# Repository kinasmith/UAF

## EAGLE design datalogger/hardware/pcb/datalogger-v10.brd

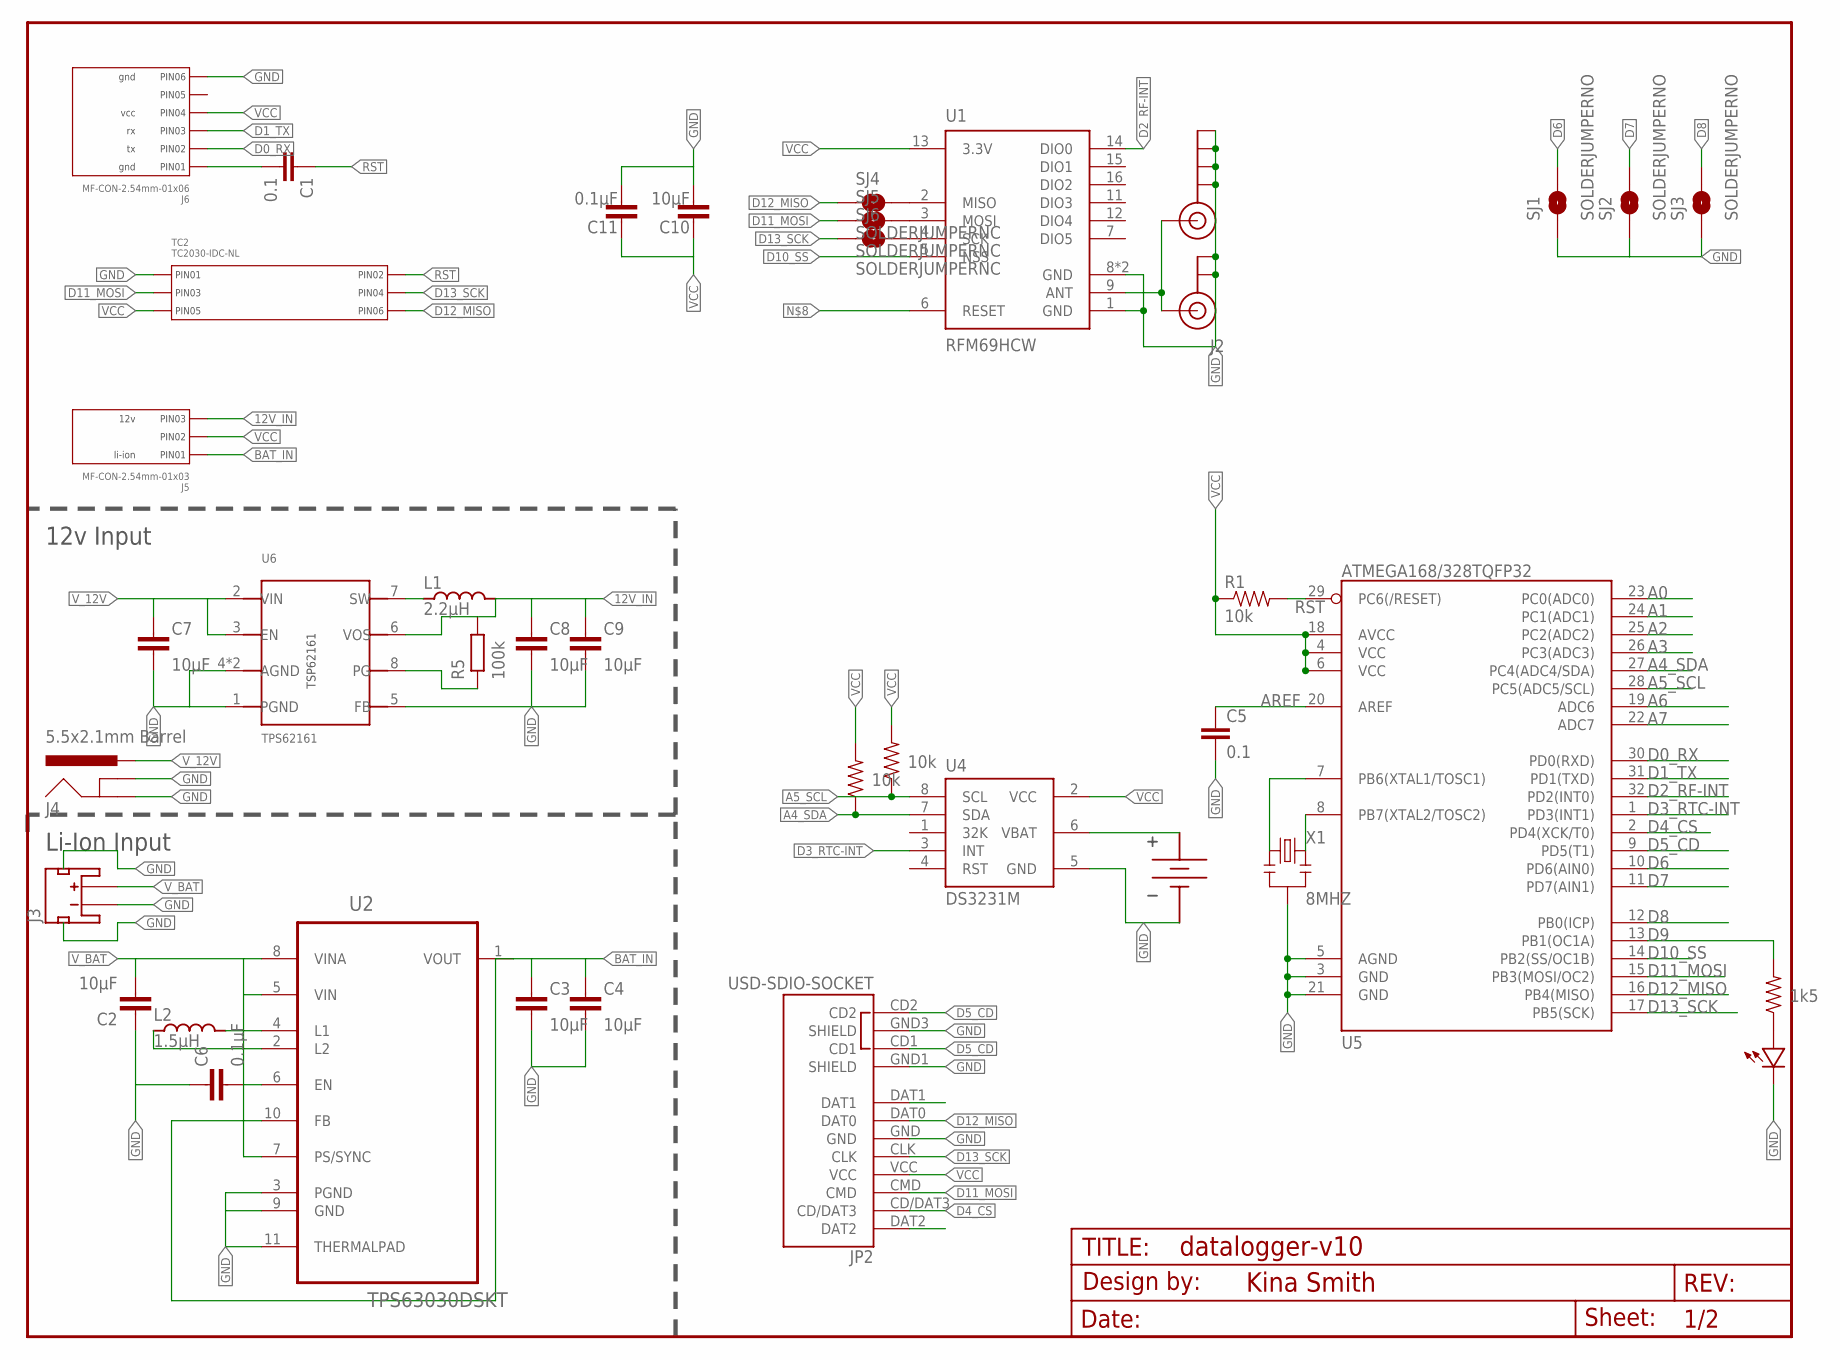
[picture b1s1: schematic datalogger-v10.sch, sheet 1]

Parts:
C1, C5: 0.1; 0603-CAP
C2, C3, C4, C7, C8, C9, C10: 10µF; C0805-N
C6, C11: 0.1µF; C0603-N
FRAME1: FRAME-LETTERNO_PACKAGE; DUMMY
J2: U.FL
J3: JST_2MM_MALE; JST-2-SMD
J4: 5.5x2.1mm Barrel; POWER_JACK_SMD
J5: MF-CON-2.54mm-01x03; PTH_2.54MM_01X03
J6: MF-CON-2.54mm-01x06; PTH_2.54MM_01X06
J$1: SMA_EDGE; SMA-EDGE
JP2: USD-SDIO-SOCKET; MICRO-SD-SOCKET-SDIO
L1: 2.2µH; IND_2.5X2
L2: 1.5µH; IND_3X3
R1, R3, R4: 10k; 0603-RES
R2: 1k5; 0603-RES
R5: 100k; R0603-N
SJ1, SJ2, SJ3: SOLDERJUMPERNO; SJ_2S-NO
SJ4, SJ5, SJ6: SOLDERJUMPERNC; SJ_2S
TC2: TC2030-IDC-NL
U1: RFM69HCW; RFM69HCW-XXXS2
U2: TPS63030DSKT; SON50P260X260X80-11N
U4: DS3231M; SO08
U5: ATMEGA168/328TQFP32; TQFP32-08
U6: TPS62161; WSON-8
U$1: BATTERY_HOLDER12MM; BATTCON_12MM
U$2: LED0603; 0603-LED
X1: 8MHZ; RESONATOR-SMD

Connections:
3V3L1: L2.P$2, U2.4 (L1)
3V3L2: L2.P$1, U2.2 (L2)
12V_IN: C8.1, C9.1, J5.P$3 (PIN3), L1.P$2, R5.2, U6.6 (VOS)
A0: U5.23 (PC0(ADC0))
A1: U5.24 (PC1(ADC1))
A2: U5.25 (PC2(ADC2))
A3: U5.26 (PC3(ADC3))
A4_SDA: R4.1, U4.7 (SDA), U5.27 (PC4(ADC4/SDA))
A5_SCL: R3.1, U4.8 (SCL), U5.28 (PC5(ADC5/SCL))
A6: U5.19 (ADC6)
A7: U5.22 (ADC7)
ANT: J2.P$3 (SIGNAL), J$1.SIG (SIGNAL), U1.9 (ANT)
AREF: C5.1, U5.20 (AREF)
BAT_IN: C3.1, C4.1, J5.P$1 (PIN1), U2.1 (VOUT), U2.10 (FB)
D0_RX: J6.P$2 (PIN2), U5.30 (PD0(RXD))
D1_TX: J6.P$3 (PIN3), U5.31 (PD1(TXD))
D2_RF-INT: U1.14 (DIO0), U5.32 (PD2(INT0))
D3_RTC-INT: U4.3 (INT), U5.1 (PD3(INT1))
D4_CS: JP2.CD/DAT3, U5.2 (PD4(XCK/T0))
D5_CD: JP2.CD1, JP2.CD2, U5.9 (PD5(T1))
D6: SJ1.2, U5.10 (PD6(AIN0))
D7: SJ2.2, U5.11 (PD7(AIN1))
D8: SJ3.2, U5.12 (PB0(ICP))
D9: R2.2, U5.13 (PB1(OC1A))
D10_SS: U1.5 (NSS), U5.14 (PB2(SS/OC1B))
D11_MOSI: JP2.CMD, SJ5.1, TC2.P$3 (PIN3), U5.15 (PB3(MOSI/OC2))
D12_MISO: JP2.DAT0, SJ4.1, TC2.P$6 (PIN6), U5.16 (PB4(MISO))
D13_SCK: JP2.CLK, SJ6.1, TC2.P$4 (PIN4), U5.17 (PB5(SCK))
GND: C2.1, C3.2, C4.2, C5.2, C6.1, C7.2, C8.2, C9.2, C10.2, C11.2, J2.P$1 (GND), J2.P$2 (GND), J3.1 (-), J3.NC1 (PAD1), J3.NC2 (PAD2), J4.GND (GNDBREAK), J4.P$4 (GND), J6.P$6 (PIN6), J$1.GND@0 (GND), J$1.GND@1 (GND), J$1.GND@2 (GND), J$1.GND@3 (GND), JP2.GND, JP2.GND1 (SHIELD), JP2.GND3 (SHIELD), SJ1.1, SJ2.1, SJ3.1, TC2.P$1 (PIN1), U1.1 (GND), U1.8 (GND), U1.10 (GND), U2.3 (PGND), U2.9 (GND), U2.11 (THERMALPAD), U4.5 (GND), U5.3 (GND), U5.5 (AGND), U5.21 (GND), U6.1 (PGND), U6.4 (AGND), U6.5 (FB), U6.P$9 (AGND), U$1.GND, U$2.MINUS, X1.2
unnamed: U5.7 (PB6(XTAL1/TOSC1)), X1.1
unnamed: R2.1, U$2.PLUS
unnamed: C1.2, J6.P$1 (PIN1)
unnamed: SJ4.2, U1.2 (MISO)
unnamed: SJ5.2, U1.3 (MOSI)
unnamed: U4.6 (VBAT), U$1.PWR@1 (VBAT), U$1.PWR@2 (VBAT)
unnamed: SJ6.2, U1.4 (SCK)
unnamed: R5.1, U6.8 (PG)
unnamed: U5.8 (PB7(XTAL2/TOSC2)), X1.3
RST: C1.1, R1.2, TC2.P$2 (PIN2), U5.29 (PC6(/RESET))
SW: L1.P$1, U6.7 (SW)
VCC: C10.1, C11.1, J5.P$2 (PIN2), J6.P$4 (PIN4), JP2.VCC, R1.1, R3.2, R4.2, TC2.P$5 (PIN5), U1.13 (3.3V), U4.2 (VCC), U5.4 (VCC), U5.6 (VCC), U5.18 (AVCC)
V_12V: C7.1, J4.VIN0 (PWR), U6.2 (VIN), U6.3 (EN)
V_BAT: C2.2, C6.2, J3.2 (+), U2.5 (VIN), U2.6 (EN), U2.7 (PS/SYNC), U2.8 (VINA)

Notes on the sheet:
12v Input
Li-Ion Input

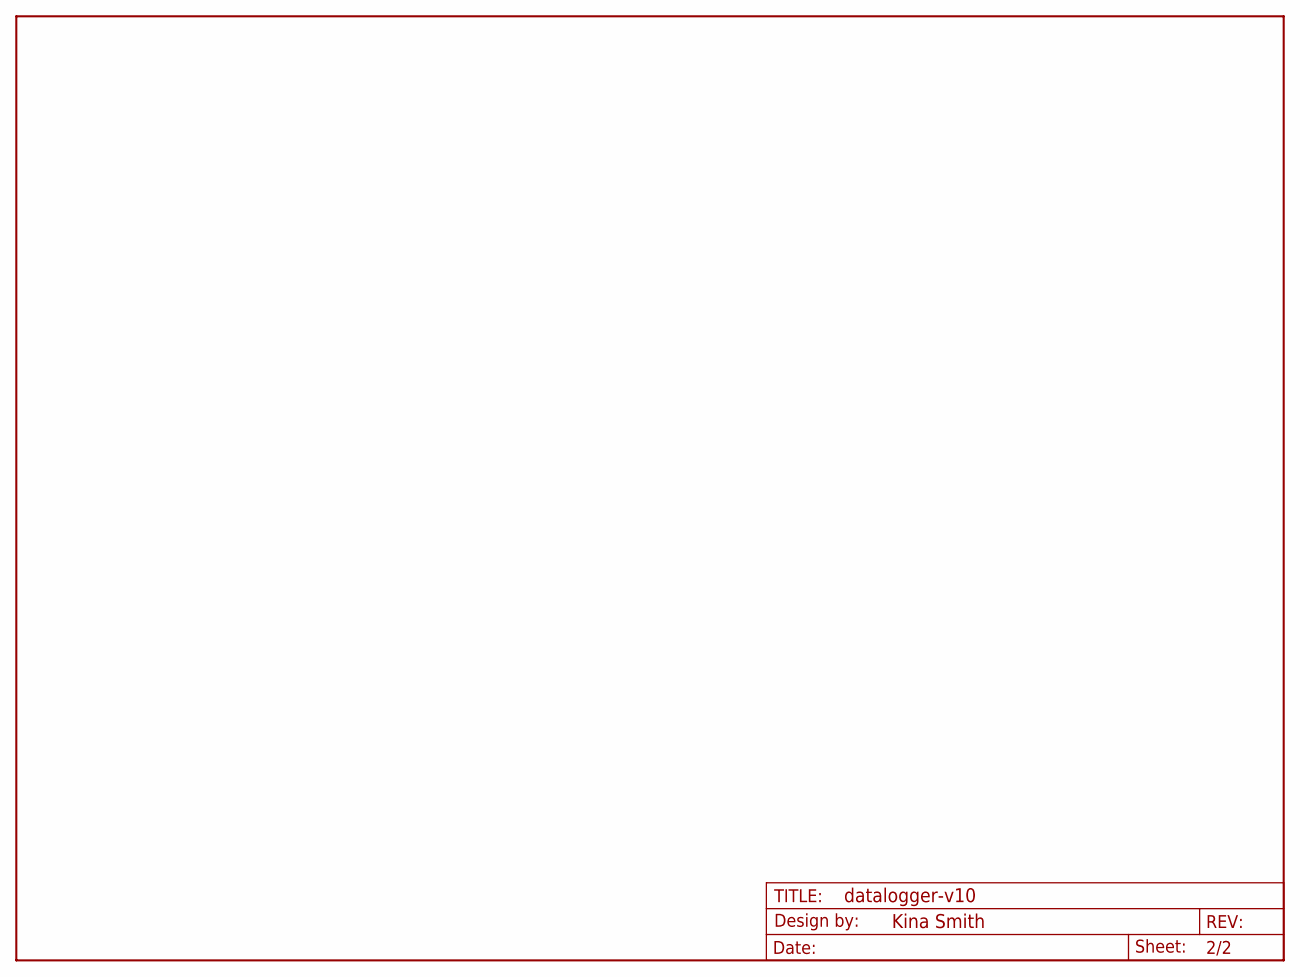
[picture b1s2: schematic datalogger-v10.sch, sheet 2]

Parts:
FRAME3: FRAME-LETTERNO_PACKAGE; DUMMY

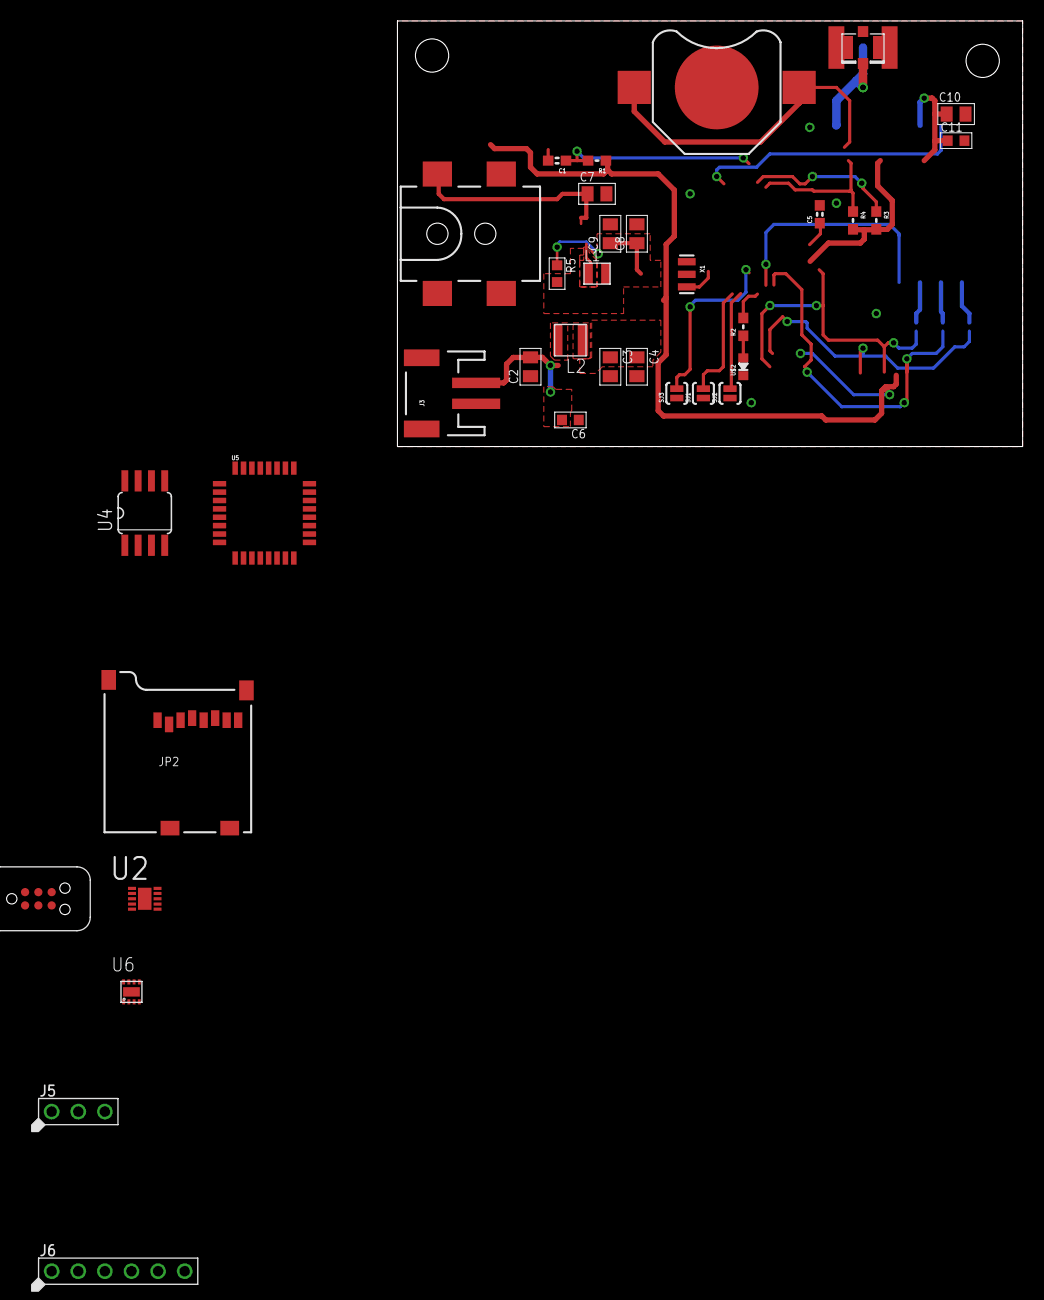
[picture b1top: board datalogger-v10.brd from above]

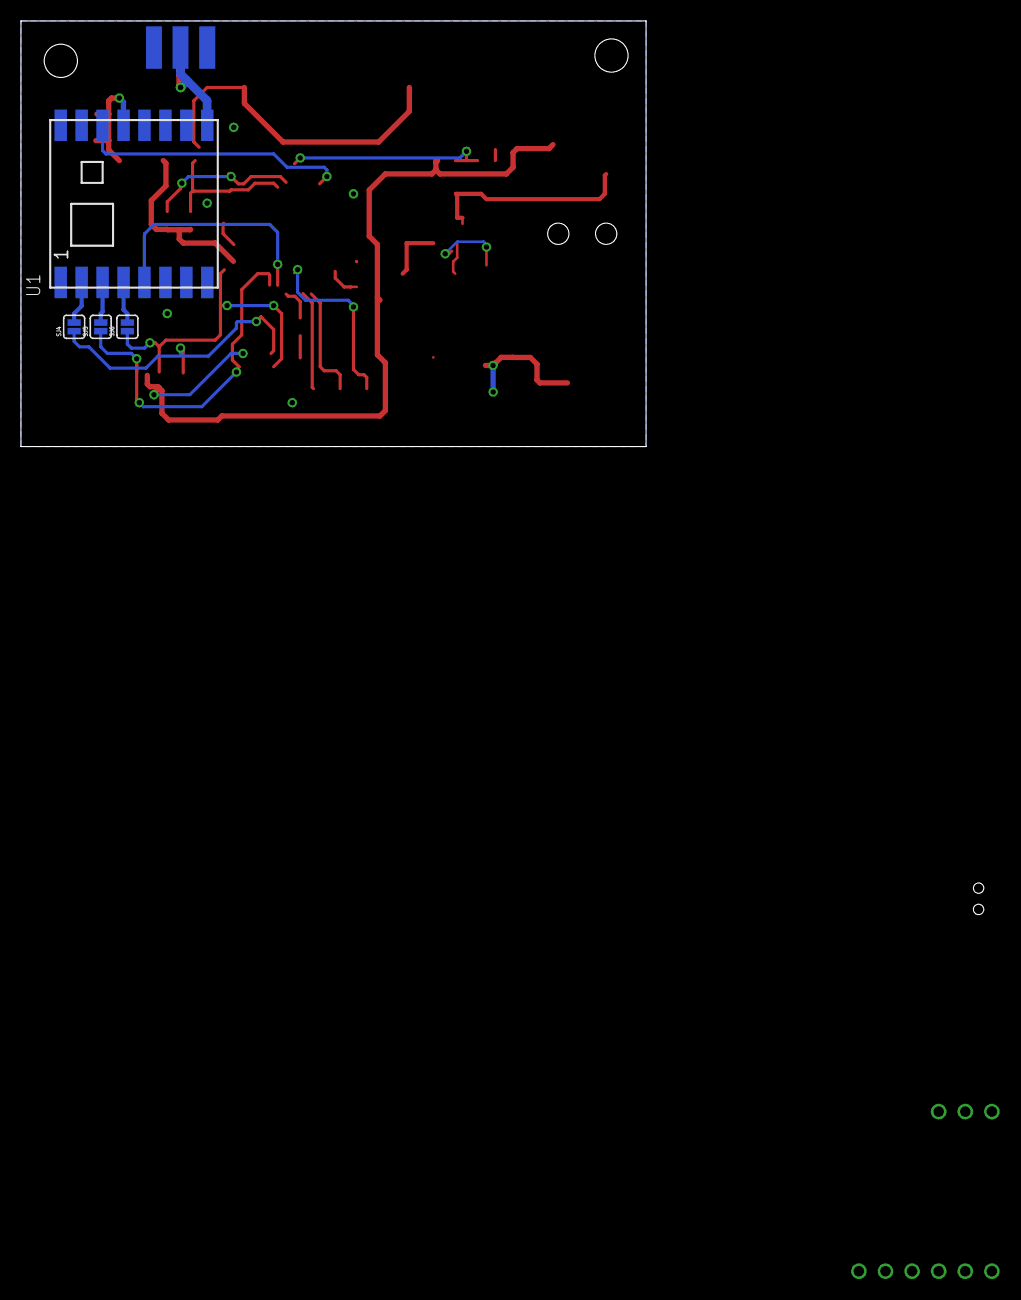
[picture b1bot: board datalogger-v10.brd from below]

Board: 2 copper layers, 59.7 x 40.6 mm, 42 parts (5 on the bottom side), 37 nets.

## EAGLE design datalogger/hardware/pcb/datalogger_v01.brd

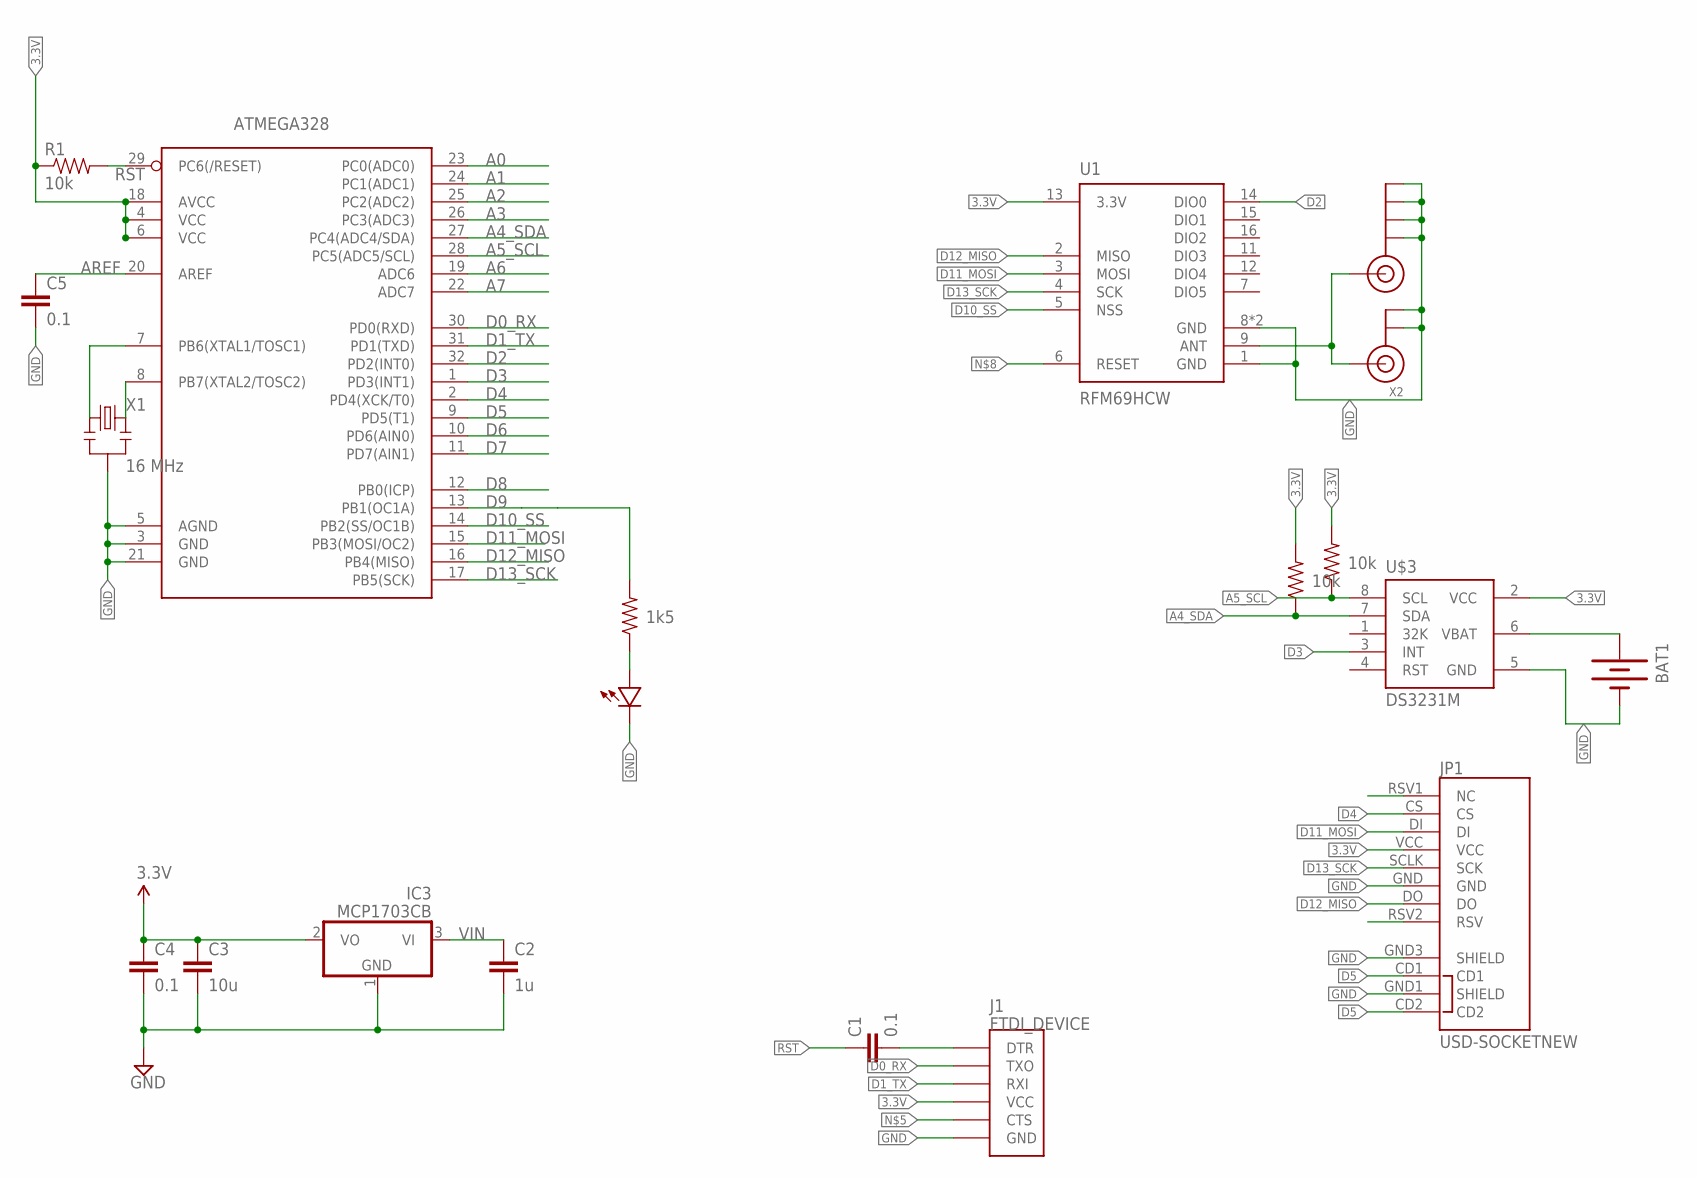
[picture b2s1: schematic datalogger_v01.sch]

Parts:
ATMEGA328: ATMega-328; TQFP32-08
BAT1: BATTERY12MM; BATTCON_12MM
C1, C4, C5: 0.1; 0603-CAP
C2: 1u; 0603-CAP
C3: 10u; 0805-CAP
IC3: MCP1703CB; SOT23
J1: FTDI_DEVICE; FTDI_DEVICE_SIDE
J$1: SMA_EDGE; SMA-EDGE
JP1: USD-SOCKETNEW; MICRO-SD-SOCKET-PP
R1, R3, R4: 10k; 0603-RES
R2: 1k5; 0603-RES
U1: RFM69HCW; RFM69HCW-XXXS2
U$2: LED0603; 0603-LED
U$3: DS3231M; SO08
X1: 16 MHz; RESONATOR-SMD
X2: ANTENNA_U.FL; U.FL

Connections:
3.3V: ATMEGA328.4 (VCC), ATMEGA328.6 (VCC), ATMEGA328.18 (AVCC), J1.P$4 (VCC), JP1.VCC, R1.1, R3.2, R4.2, U1.13 (3.3V), U$3.2 (VCC)
A0: ATMEGA328.23 (PC0(ADC0))
A1: ATMEGA328.24 (PC1(ADC1))
A2: ATMEGA328.25 (PC2(ADC2))
A3: ATMEGA328.26 (PC3(ADC3))
A4_SDA: ATMEGA328.27 (PC4(ADC4/SDA)), R4.1, U$3.7 (SDA)
A5_SCL: ATMEGA328.28 (PC5(ADC5/SCL)), R3.1, U$3.8 (SCL)
A6: ATMEGA328.19 (ADC6)
A7: ATMEGA328.22 (ADC7)
AREF: ATMEGA328.20 (AREF), C5.1
D0_RX: ATMEGA328.30 (PD0(RXD)), J1.P$2 (TXO)
D1_TX: ATMEGA328.31 (PD1(TXD)), J1.P$3 (RXI)
D2: ATMEGA328.32 (PD2(INT0)), U1.14 (DIO0)
D3: ATMEGA328.1 (PD3(INT1)), U$3.3 (INT)
D4: ATMEGA328.2 (PD4(XCK/T0)), JP1.CS
D5: ATMEGA328.9 (PD5(T1)), JP1.CD1, JP1.CD2
D6: ATMEGA328.10 (PD6(AIN0))
D7: ATMEGA328.11 (PD7(AIN1))
D8: ATMEGA328.12 (PB0(ICP))
D9: ATMEGA328.13 (PB1(OC1A)), R2.2
D10_SS: ATMEGA328.14 (PB2(SS/OC1B)), U1.5 (NSS)
D11_MOSI: ATMEGA328.15 (PB3(MOSI/OC2)), JP1.DI, U1.3 (MOSI)
D12_MISO: ATMEGA328.16 (PB4(MISO)), JP1.DO, U1.2 (MISO)
D13_SCK: ATMEGA328.17 (PB5(SCK)), JP1.SCLK (SCK), U1.4 (SCK)
GND: ATMEGA328.3 (GND), ATMEGA328.5 (AGND), ATMEGA328.21 (GND), BAT1.GND (-), C2.2, C3.2, C4.2, C5.2, IC3.1 (GND), J1.P$6 (GND), J$1.GND@0 (GND), J$1.GND@1 (GND), J$1.GND@2 (GND), J$1.GND@3 (GND), JP1.GND, JP1.GND1 (SHIELD), JP1.GND3 (SHIELD), U1.1 (GND), U1.8 (GND), U1.10 (GND), U$2.MINUS, U$3.5 (GND), X1.2, X2.1 (GND), X2.2 (GND)
unnamed: ATMEGA328.7 (PB6(XTAL1/TOSC1)), X1.1
unnamed: R2.1, U$2.PLUS
unnamed: C1.2, J1.P$1 (DTR)
unnamed: BAT1.PWR@1 (+), U$3.6 (VBAT)
unnamed: J$1.SIG (SIGNAL), U1.9 (ANT), X2.3 (SIGNAL)
unnamed: ATMEGA328.8 (PB7(XTAL2/TOSC2)), X1.3
RST: ATMEGA328.29 (PC6(/RESET)), C1.1, R1.2
VCC: C3.1, C4.1, IC3.2 (VO)
VIN: C2.1, IC3.3 (VI)

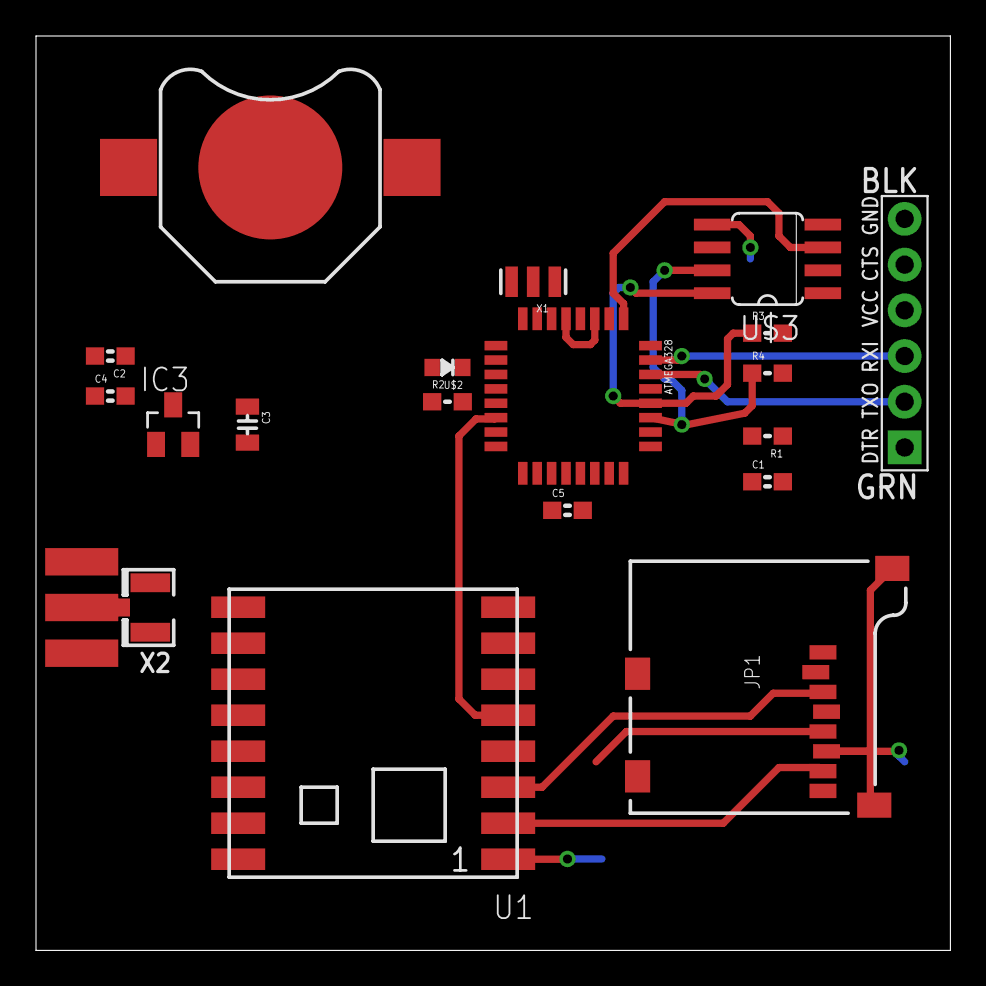
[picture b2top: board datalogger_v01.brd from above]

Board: 2 copper layers, 50.8 x 50.8 mm, 20 parts (0 on the bottom side), 25 nets.

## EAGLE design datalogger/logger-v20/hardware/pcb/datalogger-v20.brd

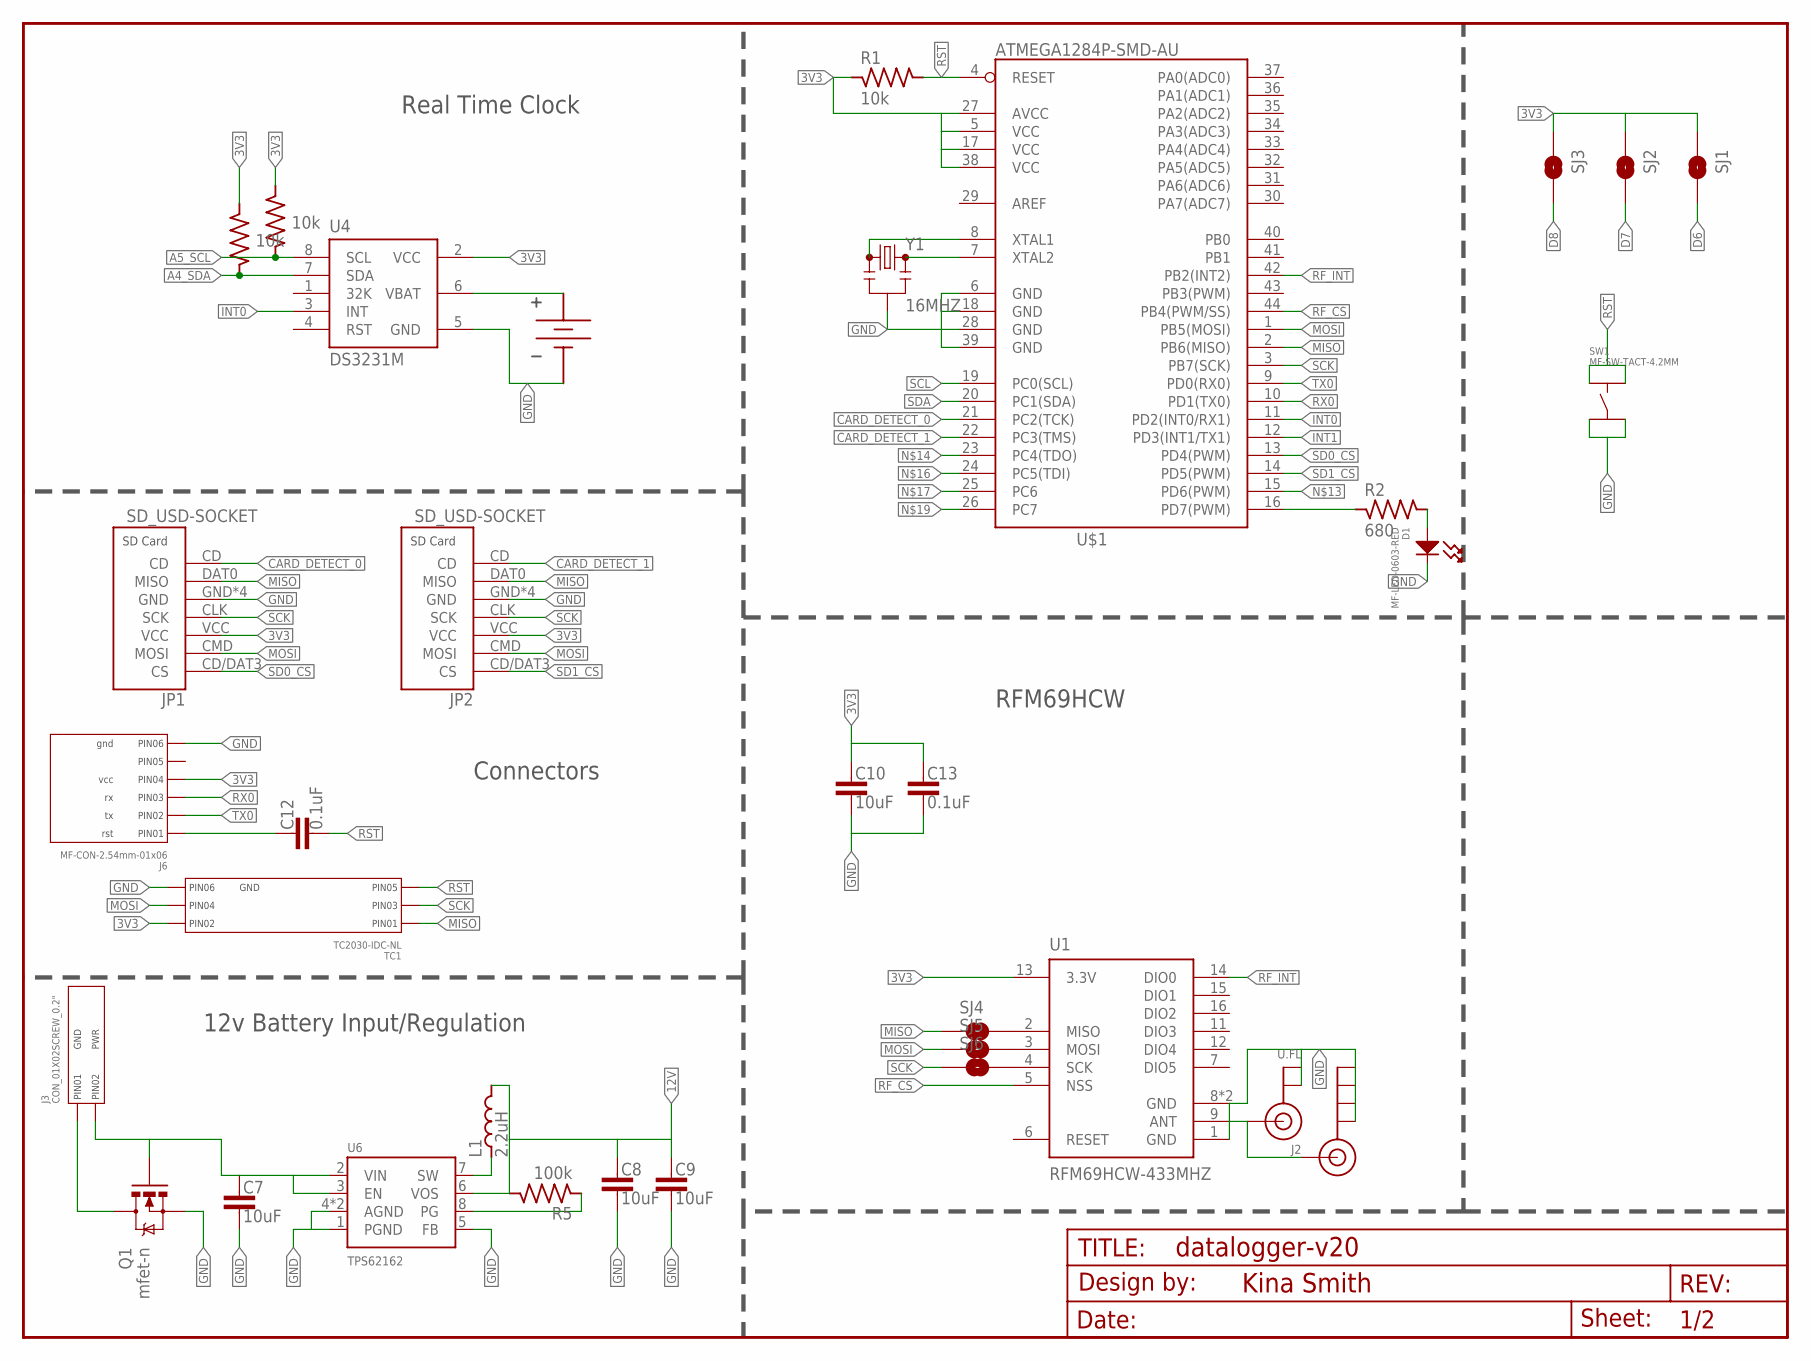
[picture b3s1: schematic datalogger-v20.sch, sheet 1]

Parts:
BAT1: BATTERY_HOLDER12MM; BAT_12MM
C7, C8, C9, C10: 10uF; C0805-N; PARTNO GRM21BR61C106KE15L
C12, C13: 0.1uF; C0603-N; PARTNO CC0603KRX7R7BB104
D1: MF-LED-0603-RED; LED0603
FRAME1: FRAME-LETTERNO_PACKAGE; DUMMY
J2: U.FL; ADAFRUIT_U.FL
J3: CON_01X02SCREW_0.2"; SCREW_TERM_2POS
J4: ANTENNA_SMA_EDGE; SMA-EDGE
J6: MF-CON-2.54mm-01x06; PTH_2.54MM_01X06; PARTNO NA
JP1, JP2: SD_USD-SOCKET; MICRO-SD-SOCKET-SDIO
L1: 2.2uH; L2520; PARTNO VLS252012T-2R2M1R3
Q1: mfet-n; SOT23-3; PARTNO SI2312BDS-T1-GE3
R1, R3, R4: 10k; R0603-N; PARTNO RC0603FR-0710KL
R2: 680; R0603-N; PARTNO RC0603FR-0710KL
R5: 100k; R0603-N; PARTNO RC0603FR-07100KL
SJ1, SJ2, SJ3, SJ4, SJ5, SJ6: JUMPER-PAD-2-NOYES_SILK; PAD-JUMPER-2-NO_YES_SILK
SW1: MF-SW-TACT-4.2MM; TACT4.2MM
TC1: TC2030-IDC-NL; PARTNO NA
U1: RFM69HCW-433MHZ; RFM69HCW-XXXS2
U4: DS3231M; SO08
U6: TPS62162; WSON-8
U$1: ATMEGA1284P-SMD-AU; TQFP44
Y1: 16MHZ; RESONATOR-SMD

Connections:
3V3: C10.1, C13.1, J6.P$4 (PIN4), JP1.VCC, JP2.VCC, R1.1, R3.2, R4.2, SJ1.1, SJ2.1, SJ3.1, TC1.P$2 (PIN2), U1.13 (3.3V), U4.2 (VCC), U$1.5 (VCC), U$1.17 (VCC), U$1.27 (AVCC), U$1.38 (VCC)
12V: C8.1, C9.1, L1.P$2, R5.2, U6.6 (VOS)
A4_SDA: R4.1, U4.7 (SDA)
A5_SCL: R3.1, U4.8 (SCL)
ANT: J2.3 (SIGNAL), J4.SIG (SIGNAL), U1.9 (ANT)
CARD_DETECT_0: JP1.CD, U$1.21 (PC2(TCK))
CARD_DETECT_1: JP2.CD, U$1.22 (PC3(TMS))
D6: SJ1.2
D7: SJ2.2
D8: SJ3.2
GND: BAT1.GND, C7.2, C8.2, C9.2, C10.2, C13.2, D1.CATHODE, J2.1 (GND), J2.2 (GND), J4.GND@0 (GND), J4.GND@1 (GND), J4.GND@2 (GND), J4.GND@3 (GND), J6.P$6 (PIN6), JP1.GND, JP1.GND1 (GND), JP1.GND2 (GND), JP1.GND3 (GND), JP2.GND, JP2.GND1 (GND), JP2.GND2 (GND), JP2.GND3 (GND), Q1.2 (S), SW1.P$3, SW1.P$4, TC1.P$6 (PIN6), U1.1 (GND), U1.8 (GND), U1.10 (GND), U4.5 (GND), U6.1 (PGND), U6.4 (AGND), U6.5 (FB), U6.P$9 (AGND), U$1.6 (GND), U$1.18 (GND), U$1.28 (GND), U$1.39 (GND), Y1.2
INT0: U4.3 (INT), U$1.11 (PD2(INT0/RX1))
INT1: U$1.12 (PD3(INT1/TX1))
MISO: JP1.DAT0 (MISO), JP2.DAT0 (MISO), SJ4.1, TC1.P$1 (PIN1), U$1.2 (PB6(MISO))
MOSI: JP1.CMD (MOSI), JP2.CMD (MOSI), SJ5.1, TC1.P$4 (PIN4), U$1.1 (PB5(MOSI))
unnamed: J3.GND (PIN1), Q1.3 (D)
unnamed: R2.1, U$1.16 (PD7(PWM))
unnamed: U$1.7 (XTAL2), Y1.3
unnamed: C12.1, J6.P$1 (PIN1)
unnamed: U$1.8 (XTAL1), Y1.1
unnamed: L1.P$1, U6.7 (SW)
unnamed: SJ4.2, U1.2 (MISO)
unnamed: D1.ANODE, R2.2
unnamed: SJ5.2, U1.3 (MOSI)
unnamed: BAT1.PWR@1 (VBAT), BAT1.PWR@2 (VBAT), U4.6 (VBAT)
unnamed: SJ6.2, U1.4 (SCK)
unnamed: R5.1, U6.8 (PG)
RF_CS: U1.5 (NSS), U$1.44 (PB4(PWM/SS))
RF_INT: U1.14 (DIO0), U$1.42 (PB2(INT2))
RST: C12.2, R1.2, SW1.P$1, SW1.P$2, TC1.P$5 (PIN5), U$1.4 (RESET)
RX0: J6.P$3 (PIN3), U$1.10 (PD1(TX0))
SCK: JP1.CLK (SCK), JP2.CLK (SCK), SJ6.1, TC1.P$3 (PIN3), U$1.3 (PB7(SCK))
SCL: U$1.19 (PC0(SCL))
SD0_CS: JP1.CD/DAT3 (CS), U$1.13 (PD4(PWM))
SD1_CS: JP2.CD/DAT3 (CS), U$1.14 (PD5(PWM))
SDA: U$1.20 (PC1(SDA))
TX0: J6.P$2 (PIN2), U$1.9 (PD0(RX0))
V_BAT: C7.1, J3.PWR (PIN2), Q1.1 (G), U6.2 (VIN), U6.3 (EN)

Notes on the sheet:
12v Battery Input/Regulation
RFM69HCW
Connectors
Real Time Clock

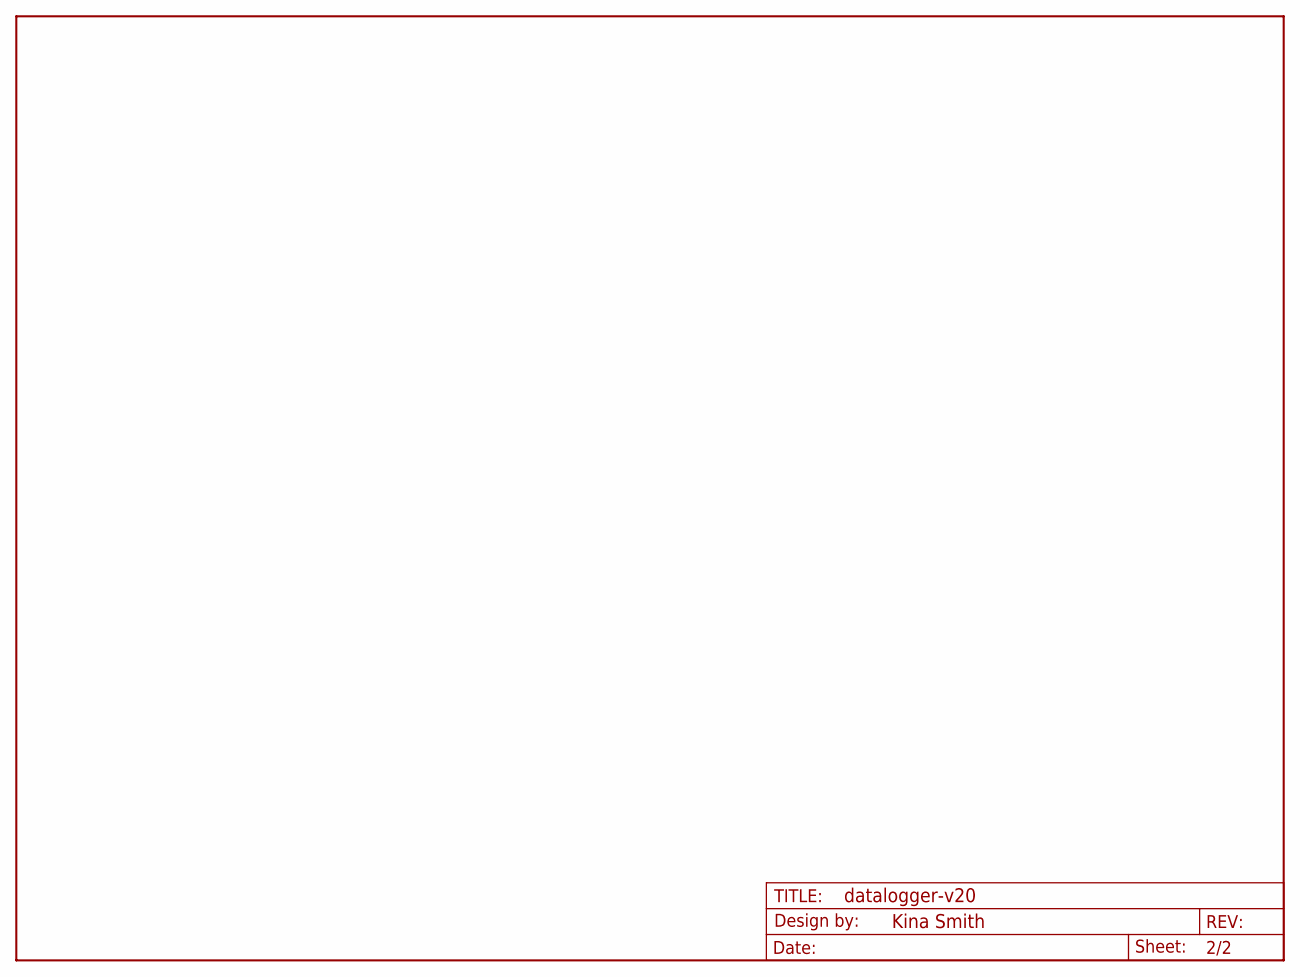
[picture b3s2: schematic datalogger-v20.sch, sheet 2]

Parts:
FRAME3: FRAME-LETTERNO_PACKAGE; DUMMY

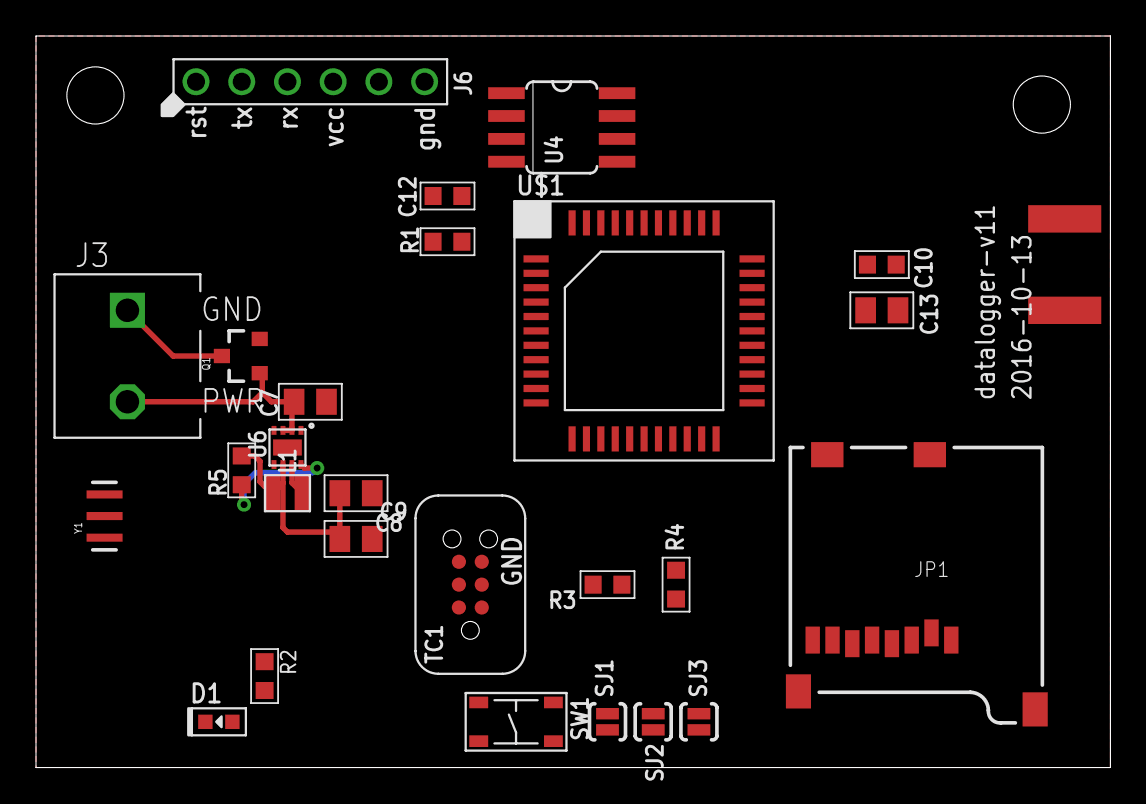
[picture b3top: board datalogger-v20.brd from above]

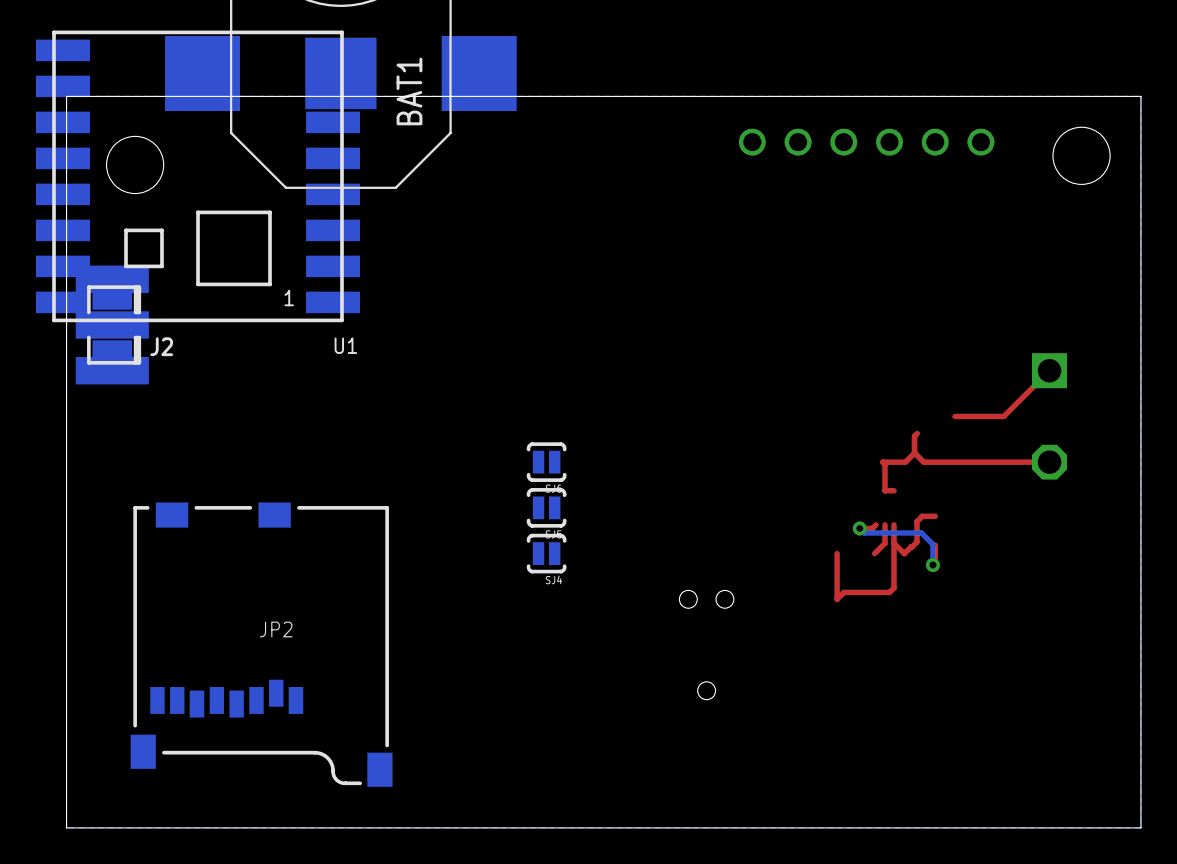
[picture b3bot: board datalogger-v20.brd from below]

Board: 2 copper layers, 59.7 x 40.6 mm, 36 parts (8 on the bottom side), 32 nets.

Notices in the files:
parts and their libraries:
SparkFun-Connectors: Licensing: Creative Commons ShareAlike 4.0 International - https://creativecommons.org/licenses/by-sa/4.0
SparkFun-Connectors: Licensing: CC v3.0 Share-Alike You are welcome to use this library for commercial purposes.
